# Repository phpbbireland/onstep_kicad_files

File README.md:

# onstep_kicad_files
Kicad Support Files for OnStep

Here I will Add support files for developing OnStep with Kicad (& FreeCAD where available)...

I have issues access my git repos... appears to be a password/username mismatch... no idea what's up...

The folder: Controller_Version_5.0_SMD_Git contains dev material and is not currently working... possible track errors...

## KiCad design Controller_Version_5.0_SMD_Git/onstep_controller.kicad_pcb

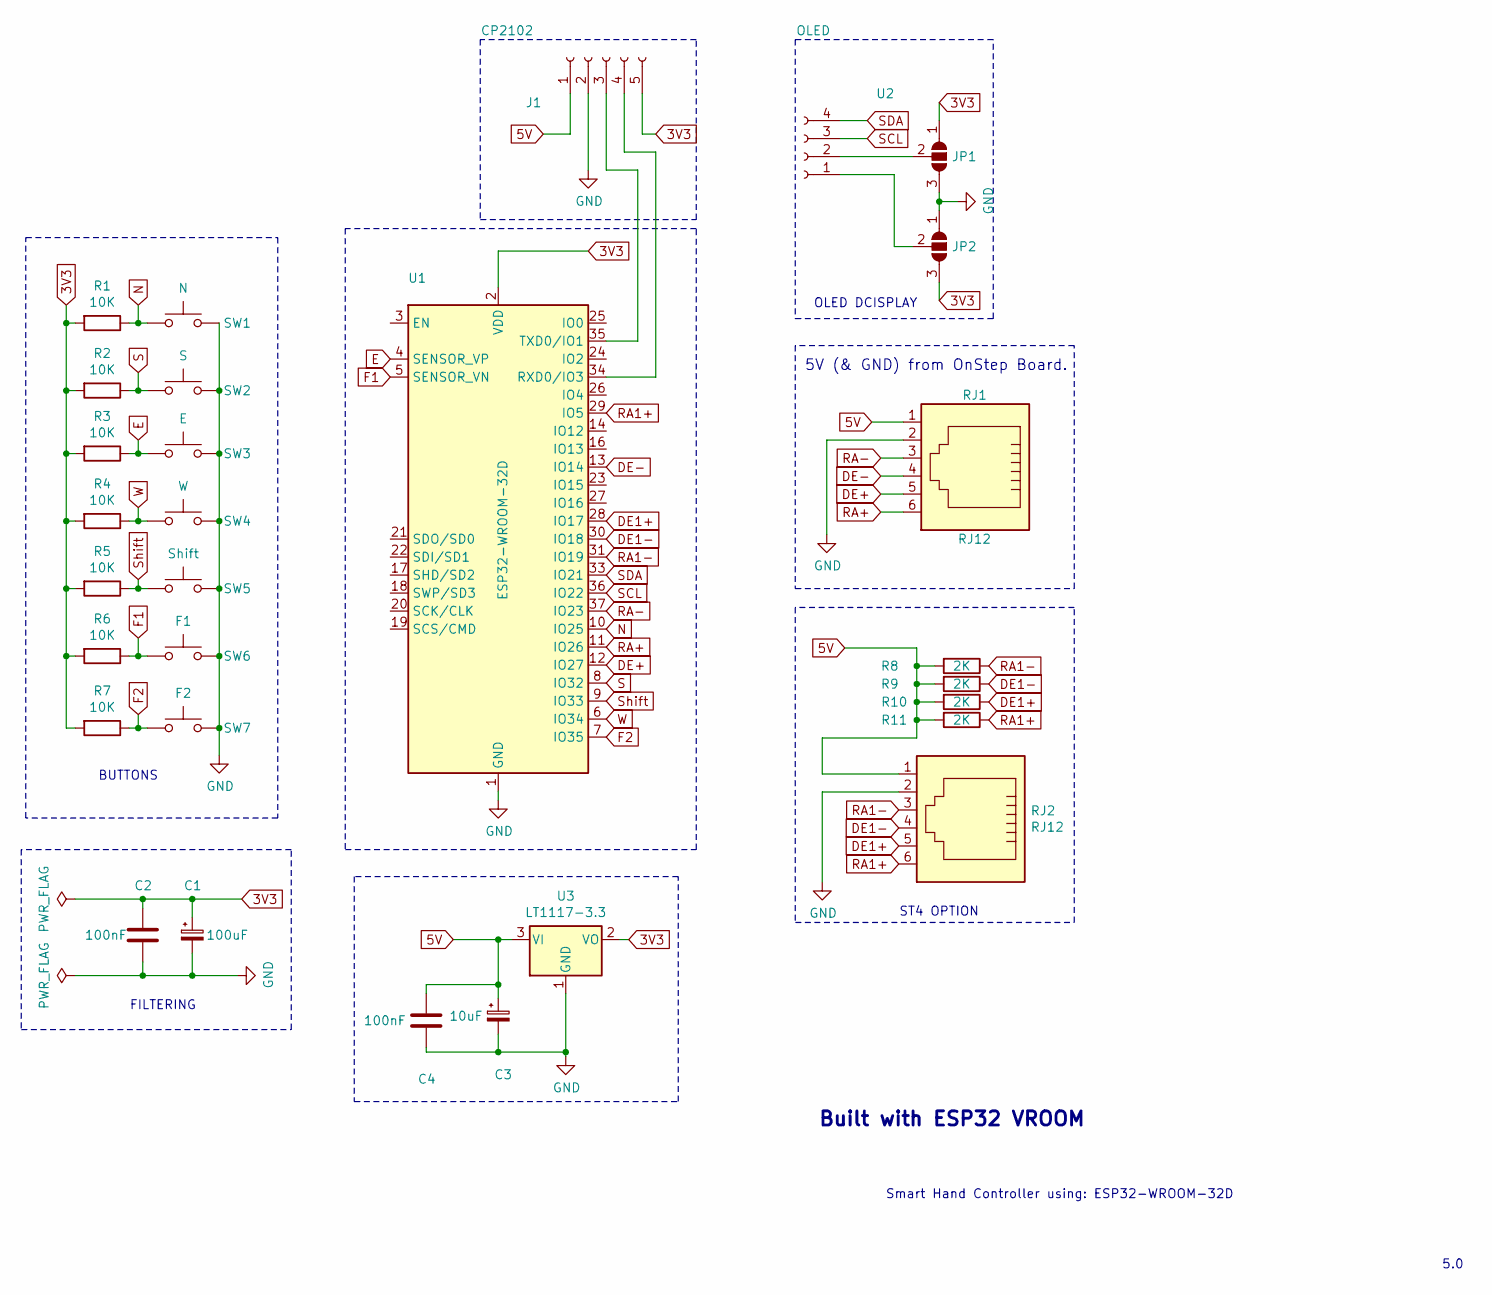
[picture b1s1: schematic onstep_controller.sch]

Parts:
C1: 100uF; CP_Radial_D8.0mm_P5.00mm
C2: 100nF; C_1206_3216Metric_Pad1.42x1.75mm_HandSolder
C3: 10uF; CP_Radial_D8.0mm_P5.00mm
C4: 100nF; C_0805_2012Metric_Pad1.15x1.40mm_HandSolder
J1: CP2102; PinSocket_1x05_P2.54mm_Horizontal
JP1, JP2: SolderJumper_3_Open; SolderJumper-3_P1.3mm_Open_Pad1.0x1.5mm_NumberLabels
R1, R2, R3, R4, R5, R6, R7: 10K; R_0805_2012Metric_Pad1.15x1.40mm_HandSolder
R8, R9, R10, R11: 2K; R_0805_2012Metric_Pad1.15x1.40mm_HandSolder
RJ1, RJ2: RJ12; RJ12_IreR2
SW1: N; SW_PUSH-12mm_
SW2: S; SW_PUSH-12mm_
SW3: E; SW_PUSH-12mm_
SW4: W; SW_PUSH-12mm_
SW5: Shift; SW_PUSH-12mm_
SW6: F1; SW_PUSH-12mm_
SW7: F2; SW_PUSH-12mm_
U1: ESP32-WROOM-32D; ESP32-WROOM-32x
U2: OLED; PinSocket_1x04_P2.54mm_Vertical
U3: LT1117-3.3; SOT-223-3_TabPin2

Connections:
3V3: C1.1, C2.1, J1.5, JP1.1 (A), JP2.3 (B), R1.2, R2.2, R3.2, R4.2, R5.2, R6.2, R7.2, U1.2 (VDD), U3.2 (VO)
5V: C3.1, C4.1, J1.1, R8.2, R9.2, R10.2, R11.2, RJ1.1, RJ2.1, U3.3 (VI)
DE1+: R10.1, RJ2.5, U1.28 (IO17)
DE1-: R9.1, RJ2.4, U1.30 (IO18)
DE+: RJ1.5, U1.12 (IO27)
DE-: RJ1.4, U1.13 (IO14)
E: R3.1, SW3.1, U1.4 (SENSOR_VP)
F1: R6.1, SW6.1, U1.5 (SENSOR_VN)
F2: R7.1, SW7.1, U1.7 (IO35)
GND: C1.2, C2.2, C3.2, C4.2, J1.2, JP1.3 (B), JP2.1 (A), RJ1.2, RJ2.2, SW1.2, SW2.2, SW3.2, SW4.2, SW5.2, SW6.2, SW7.2, U1.1 (GND), U1.15 (GND), U1.38 (GND), U3.1 (GND)
N: R1.1, SW1.1, U1.10 (IO25)
unnamed: J1.3, U1.35 (TXD0/IO1)
unnamed: J1.4, U1.34 (RXD0/IO3)
unnamed: JP1.2 (C), U2.2
unnamed: JP2.2 (C), U2.1
RA1+: R11.1, RJ2.6, U1.29 (IO5)
RA1-: R8.1, RJ2.3, U1.31 (IO19)
RA+: RJ1.6, U1.11 (IO26)
RA-: RJ1.3, U1.37 (IO23)
S: R2.1, SW2.1, U1.8 (IO32)
SCL: U1.36 (IO22), U2.3
SDA: U1.33 (IO21), U2.4
Shift: R5.1, SW5.1, U1.9 (IO33)
W: R4.1, SW4.1, U1.6 (IO34)

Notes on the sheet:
Smart Hand Controller using: ESP32-WROOM-32D
5.0
Built with ESP32 VROOM
5V (& GND) from OnStep Board.
OLED DCISPLAY
ST4 OPTION
FILTERING
BUTTONS

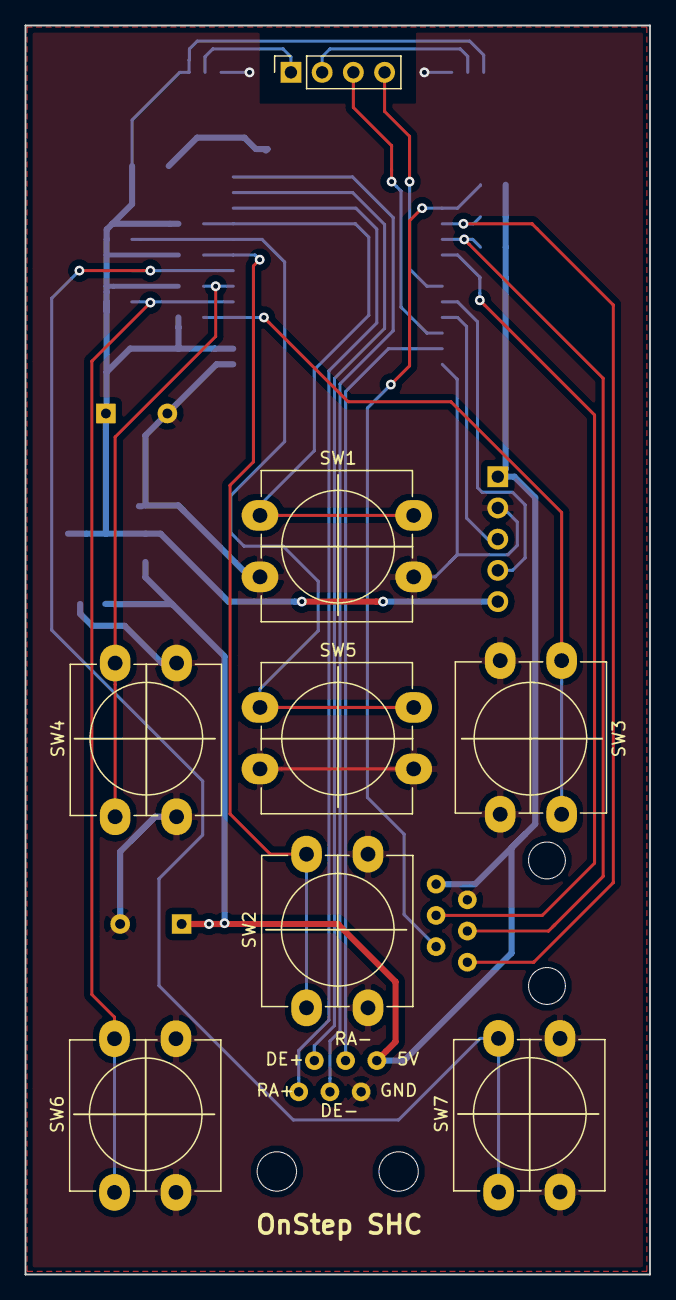
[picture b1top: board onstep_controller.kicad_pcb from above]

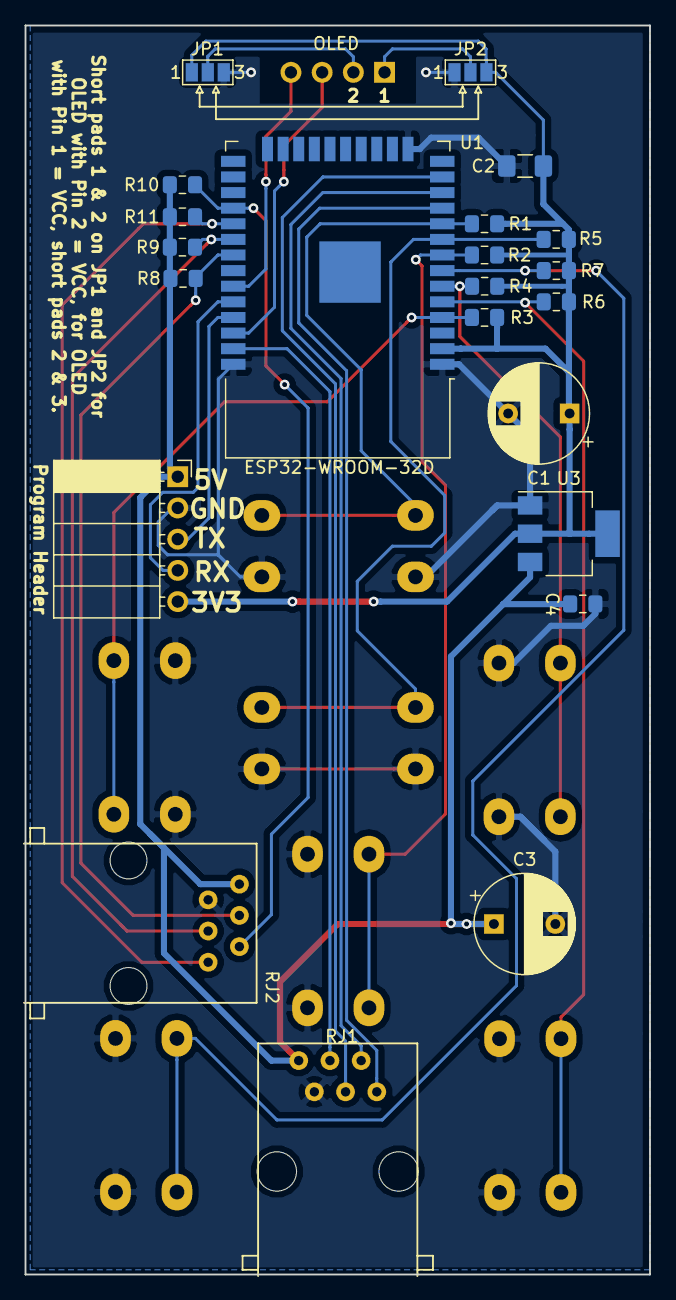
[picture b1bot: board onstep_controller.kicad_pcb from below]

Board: 2 copper layers, 50.8 x 101.6 mm, 30 parts (22 on the bottom side), 24 nets.

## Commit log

2020-08-01 Adding Test File BluePill Step
2020-08-01 More test files
2020-08-01 Two more test files
    I can't access from git directly... no idea why...
2020-08-01 Update...
2020-10-15 Adding OnStep SHC using Wroom Version
    Smart Hand Controller using: ESP32-WROOM-32D
2020-10-16 Adding notice re dev folder issues
